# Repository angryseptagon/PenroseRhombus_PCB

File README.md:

# penroserombus_PCB
PCBs to make penrose tilings with addressable LEDs. in order to make a continous data signal, the data follows marking shown on PCB. these markings form closed loops, however loops can be merged using the switch onboard. They link together using 5mm U shaped single row connectors.
|P3 tiling|P2 tiling|
|-----------|------------|
|  |  |
|||

how switch position routes data:

Materials per board:

4x SK6812 (or compatable ws2812b) 5050 leds - https://www.aliexpress.com/item/32814778563.html?spm=a2g0o.cart.0.0.119f3c00zzKG71&mp=1

4x 1x3 female 2.54 mm spaced headers - https://a.aliexpress.com/_mLI1pO5

4x 100 nf decoupling capacitors in 0805 size - 

?x 5mm U shaped connectors 2.54mm spacing. - https://www.aliexpress.com/item/4001034220522.html?spm=a2g0o.cart.0.0.74ea3c00vI7Rsv&mp=1

1x dpdt MSS22D18 switch - https://www.aliexpress.com/item/4000684780091.html?spm=a2g0o.cart.0.0.4ff63c00xiN8D5&mp=1

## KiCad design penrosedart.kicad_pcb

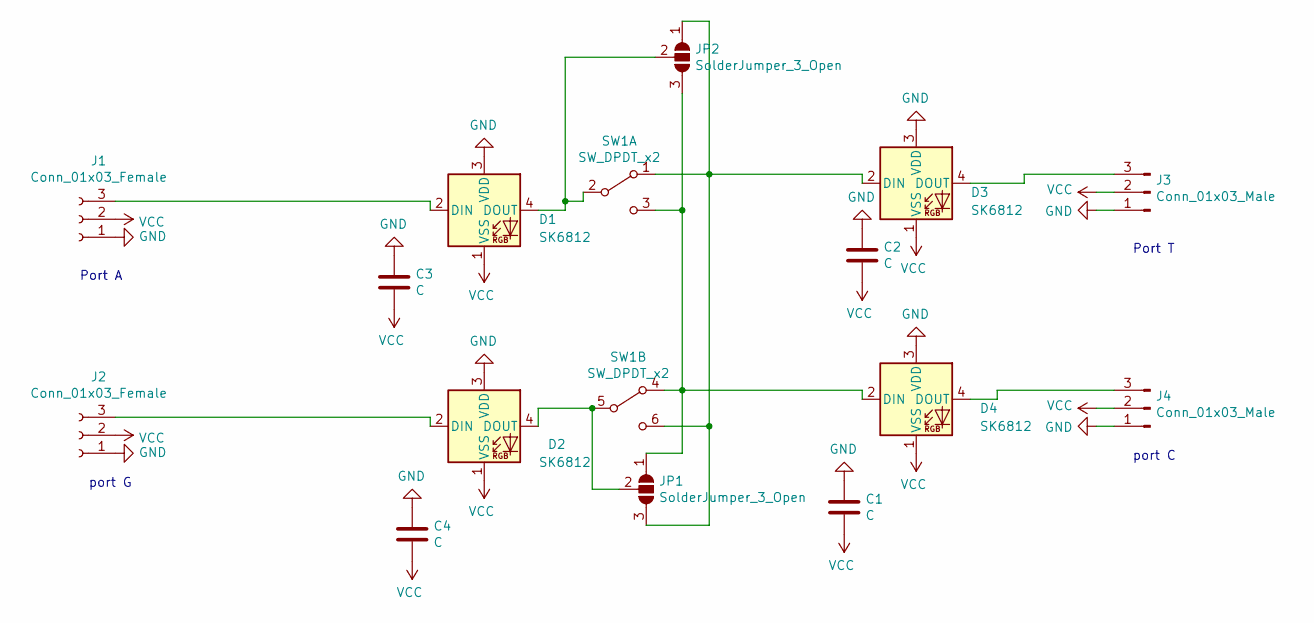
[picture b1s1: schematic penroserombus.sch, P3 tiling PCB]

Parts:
C1, C2, C3, C4: C; C_0805_2012Metric_Pad1.18x1.45mm_HandSolder
D1, D2, D3, D4: SK6812; LED_SK6812_PLCC4_5.0x5.0mm_P3.2mm
J1, J2: Conn_01x03_Female; PinSocket_1x03_P2.54mm_Vertical
J3, J4: Conn_01x03_Male; PinSocket_1x03_P2.54mm_Vertical
JP1, JP2: SolderJumper_3_Open; SolderJumper-3_P1.3mm_Open_RoundedPad1.0x1.5mm
SW1: SW_DPDT_x2; Aliexpress_slideswitch_2P2T

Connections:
GND: C1.1, C2.1, C3.1, C4.1, D1.3 (VDD), D2.3 (VDD), D3.3 (VDD), D4.3 (VDD), J1.1, J2.1, J3.1, J4.1
unnamed: D1.2 (DIN), J1.3
unnamed: D1.4 (DOUT), JP2.2 (C), SW1.2 (B)
unnamed: D2.2 (DIN), J2.3
unnamed: D2.4 (DOUT), JP1.2 (C), SW1.5 (B)
unnamed: D3.2 (DIN), JP1.3 (B), JP2.1 (A), SW1.1 (A), SW1.6 (C)
unnamed: D3.4 (DOUT), J3.3
unnamed: D4.2 (DIN), JP1.1 (A), JP2.3 (B), SW1.3 (C), SW1.4 (A)
unnamed: D4.4 (DOUT), J4.3
VCC: C1.2, C2.2, C3.2, C4.2, D1.1 (VSS), D2.1 (VSS), D3.1 (VSS), D4.1 (VSS), J1.2, J2.2, J3.2, J4.2

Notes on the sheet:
port G
port C
Port A
Port T

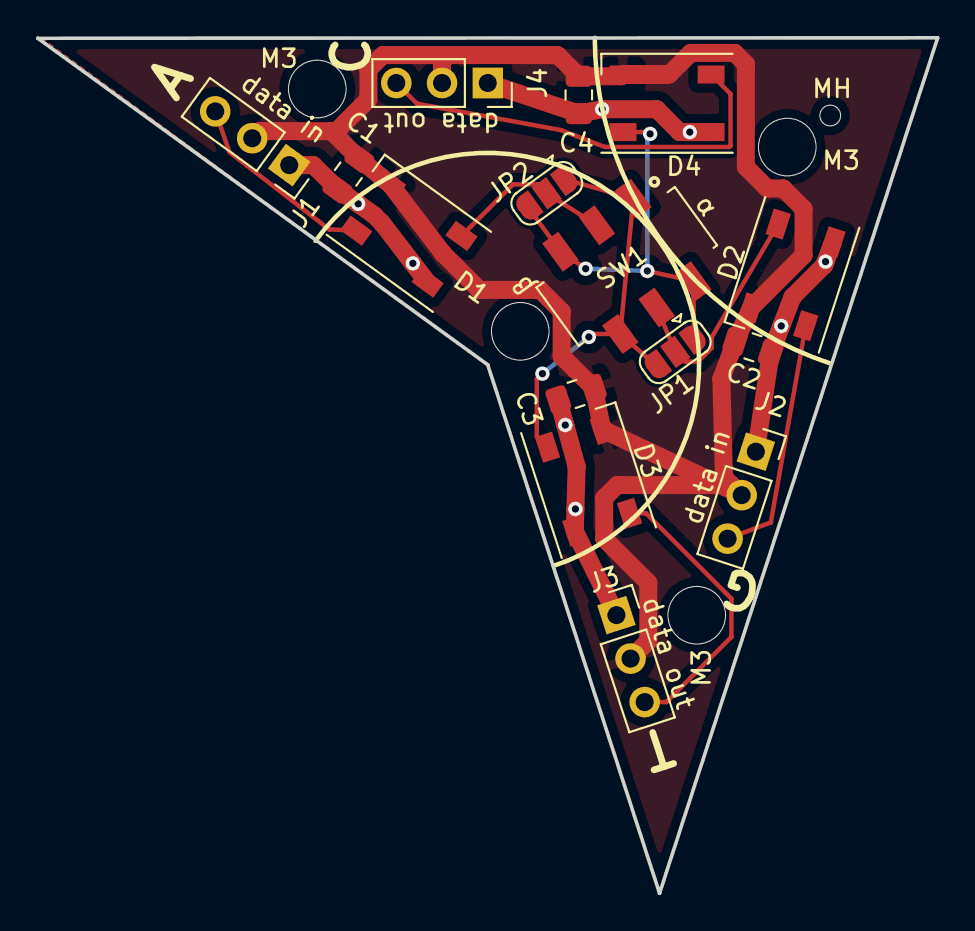
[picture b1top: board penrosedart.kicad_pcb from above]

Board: 2 copper layers, 50.0 x 47.5 mm, 20 parts (0 on the bottom side), 10 nets.

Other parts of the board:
M3, M3#2, M3#3, M3#4: MountingHole_3.2mm_M3_ISO7380
MH: Pushpin_mountinghole

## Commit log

2021-01-06 initial upload
    learning how to use github, might goof it up
2021-01-06 initial upload
    idk whats going on anymore
2021-01-06 deleting some trash
2021-01-06 ok third time is a charm
2021-01-06 added 3d model of switch from softegg's project
2021-01-06 images
2021-01-06 updated gerbers
2021-01-06 organizing
2021-01-07 added more mounting holes and generated gerbers
2021-01-09 changed out 5050 leds for 2020 led
2021-01-10 made 3535 led version
2021-01-11 added mounting holes
2021-01-12 updated thick rombus
2021-01-13 board has 4 leds instead of 2.
2021-01-13 fixed led 4 orientation
2021-01-13 updated thick rombus gerbers.
2021-01-14 rearranged leds a bit.
2021-01-14 made gerbers
2021-01-17 small tweaks to traces
2021-01-17 updated gerber zip files
2021-01-20 added kite and dart tiling
    idk why im doing this
2021-01-21 shifted ports on penrose rhombi to enforce all matching rules. fixed flipped ports on penrose dart.
    going to make new gerbers later.
2021-01-22 updated gerbers and images. new gerbers of rombi now enforce the tiling rules by making ports misalign when.
2021-01-22 fixed typo
2021-01-22 small tweaks to thick rhombus.
    shifted letters and moved jumpers closer to switch
2021-01-23 Added link
2021-01-25 increased mounting hole size to M3
    increased mounting hole size to M3 to accomidate plastic adhesive mounting hole standoffs. makes the silkscreen a bit cramped and the VCC route a bit long, but maybe I will make the top pour VCC inst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
2021-01-25 fixed 3d render image of thick rhombus.
2021-01-26 updated penrose dart with powerplane
2021-01-29 board wiring changes and mounting hole additions for adhesive standoffs
    changed top copper fill to VCC and added mounting holes with new footprint to check if the mounts collided.
2021-02-14 minor tweaks and diagrams
    Tweaks to silkscreen and stuff also added a diagram to explain switch on board. Also made top layer VCC on penrose kite.
2021-02-14 updated 3d renders
2021-02-19 added even more mounting holes
    honestly these boards are starting to look like swiss cheese but seeing how prototyping is expensive, I want to have my bases covered.
2021-03-02 leftover miscellaneous updates.
